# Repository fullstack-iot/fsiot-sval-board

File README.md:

# fsiot-sval-board
Simple Demo IoT board made using KiCad to demonstrate my skills in Full Stack IoT Development.

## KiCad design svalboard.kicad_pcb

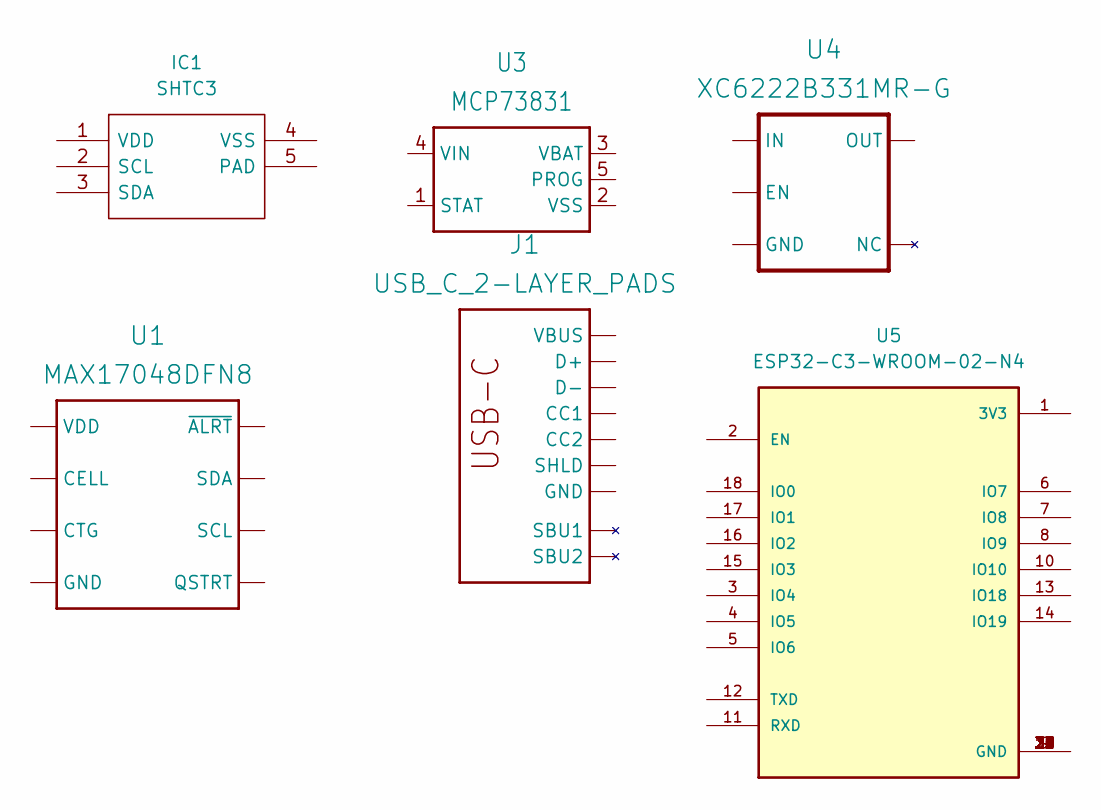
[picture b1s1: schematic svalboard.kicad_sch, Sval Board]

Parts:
IC1: SHTC3; Sensirion_DFN-4-1EP_2x2mm_P1mm_EP0.7x1.6mm; Mouser Part Number 403-SHTC3
J1: USB_C_2-LAYER_PADS; USB-C-16P-2LAYER-PADS
U1: MAX17048DFN8; DFN-8-1EP_2x2mm_P0.5mm_EP0.9x1.6mm
U3: MCP73831; SOT-23-5
U4: XC6222B331MR-G; SOT-23-5
U5: ESP32-C3-WROOM-02-N4; MODULE_ESP32-C3-WROOM-02-H4

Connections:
unnamed: J1.A6 (D+), J1.B6 (D+)
unnamed: J1.A7 (D-), J1.B7 (D-)
unnamed: J1.GND, J1.GND2 (GND)
unnamed: J1.SHLD1 (SHLD), J1.SHLD2 (SHLD), J1.SHLD3 (SHLD), J1.SHLD4 (SHLD)
unnamed: J1.VBUS1 (VBUS), J1.VBUS2 (VBUS)
unnamed: U1.4 (GND), U1.9 (GND)
unnamed: U5.9 (GND), U5.19 (GND), U5.20 (GND), U5.21 (GND), U5.22 (GND), U5.23 (GND), U5.24 (GND), U5.25 (GND), U5.26 (GND), U5.27 (GND), U5.28 (GND), U5.29 (GND), U5.30 (GND), U5.31 (GND), U5.32 (GND), U5.33 (GND), U5.34 (GND), U5.35 (GND), U5.36 (GND), U5.37 (GND), U5.38 (GND), U5.39 (GND)

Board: 2 copper layers, 6 parts (0 on the bottom side), 7 nets, no tracks yet.

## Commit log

2022-12-23 feat(PRJ): first project file commit
    Empty Kicad project files
2022-12-23 chore(GITIGNORE): update gitignore
2022-12-26 feat(PN): add some part to sch/pcb
2022-12-27 feat(PCB): add parts and 3d
2022-12-28 feat(BOARD): update parts in separate libs
